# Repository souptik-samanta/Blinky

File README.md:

# Blinky Board

Made by Souptik!

I built this little project because I wanted a heart-shaped PCB that I could gift to someone. It's a simple LED chaser built around a 555 timer and a CD4017 decade counter. The LEDs light up one after another, creating a blinking animation around the heart.

Built using parts I already had on hand, and manufactured through JLC thanks stasis.
BUILD PHOTO

and here is the bottom

worknig video 

https://youtube.com/shorts/QsSJmAaTk8Q?feature=share
## Photos

## How It Works

A 555 timer is configured as an oscillator that generates clock pulses. These pulses are fed into a CD4017 decade counter, which turns on one output at a time. Each output drives an LED on the heart, creating a rotating blinking effect. The potentiometer can be adjusted to change the animation speed.

## Bill of Materials (BoM)

| Part | Purpose | Quantity |
|--------|---------|----------|
| PCB | Heart-shaped board that holds all the components | 1 |
| LED | Creates the chasing light effect around the heart | 10 |
| 1kΩ Resistor | Helps set the oscillator timing | 1 |
| 470Ω Resistor | Limits LED current | 1 |
| Potentiometer (RV) | Adjusts the animation speed | 1 |
| 1µF Capacitor | Works with the 555 timer to generate clock pulses | 1 |
| 1x01 Header | Test/debug connection point | 1 |
| 1x02 Header | Power input connector | 1 |
| CD4017 | Sequences the LEDs one after another | 1 |
| NE555P | Generates the clock signal | 1 |

## Cost

All components were sourced from my existing parts inventory, so the project itself cost me nothing to assemble.

| Item | Cost (USD) |
|--------|------------|
| Components | $0.00 |
| PCB | JLC sponser |
| **Total Out-of-Pocket Cost** | **$0.00** |

## Why I Made It

I wanted to make something small, simple, and fun that could be gifted to someone. Instead of a regular rectangular PCB, I designed it in the shape of a heart and added a classic 555 + 4017 LED chaser circuit to make it feel a bit more special.

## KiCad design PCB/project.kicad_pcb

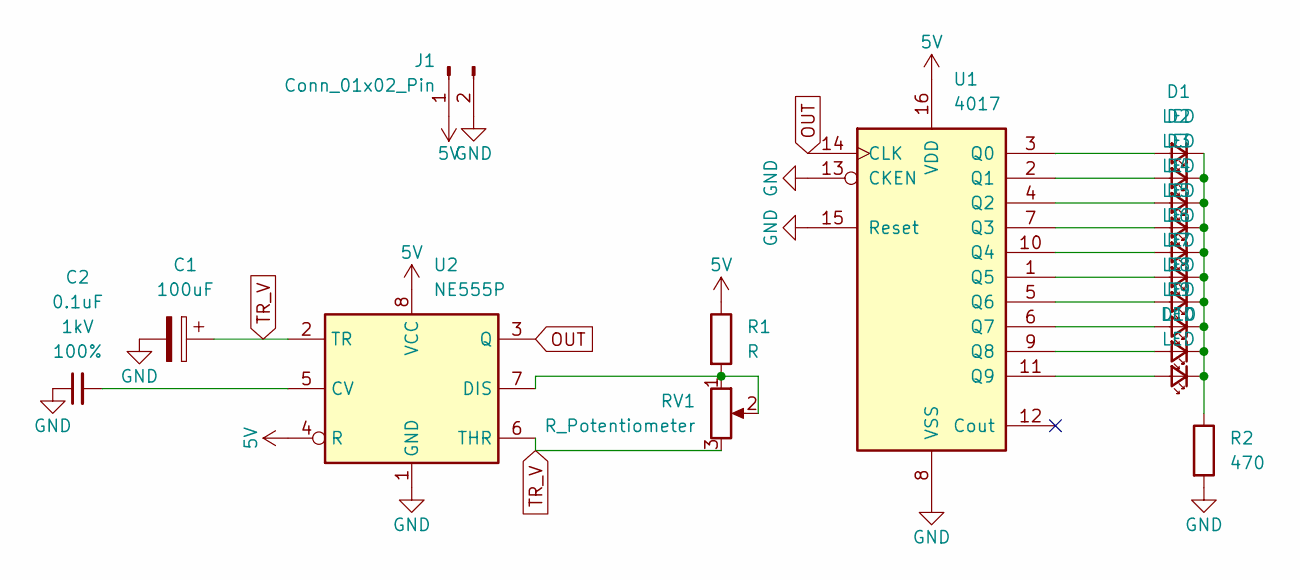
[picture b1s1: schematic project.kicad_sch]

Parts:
C1: 100uF; CP_Radial_D5.0mm_P2.50mm
C2: 0.1uF; C_Disc_D4.7mm_W2.5mm_P5.00mm; Voltage 1kV; Tolerance 100%
D1, D2, D3, D4, D5, D6, D7, D8, D9, D10: LED; LED_D5.0mm
J1: Conn_01x02_Pin; PinSocket_1x02_P2.54mm_Vertical
R1: R; R_Axial_DIN0207_L6.3mm_D2.5mm_P7.62mm_Horizontal
R2: 470; R_Axial_DIN0207_L6.3mm_D2.5mm_P7.62mm_Horizontal
RV1: R_Potentiometer; Potentiometer_Vishay_T93YA_Vertical
U1: 4017; DIP-16_W7.62mm_LongPads
U2: NE555P; DIP-8_W7.62mm_LongPads

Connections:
5V: J1.1, R1.1, U1.16 (VDD), U2.4 (R), U2.8 (VCC)
GND: C1.2, C2.1, J1.2, R2.2, U1.8 (VSS), U1.13 (CKEN), U1.15 (Reset), U2.1 (GND)
unnamed: D1.2 (A), U1.3 (Q0)
unnamed: D1.1 (K), D2.1 (K), D3.1 (K), D4.1 (K), D5.1 (K), D6.1 (K), D7.1 (K), D8.1 (K), D9.1 (K), D10.1 (K), R2.1
unnamed: D2.2 (A), U1.2 (Q1)
unnamed: D3.2 (A), U1.4 (Q2)
unnamed: D4.2 (A), U1.7 (Q3)
unnamed: D5.2 (A), U1.10 (Q4)
unnamed: D6.2 (A), U1.1 (Q5)
unnamed: D7.2 (A), U1.5 (Q6)
unnamed: D8.2 (A), U1.6 (Q7)
unnamed: D9.2 (A), U1.9 (Q8)
unnamed: D10.2 (A), U1.11 (Q9)
unnamed: C2.2, U2.5 (CV)
unnamed: R1.2, RV1.1, RV1.2, U2.7 (DIS)
OUT: U1.14 (CLK), U2.3 (Q)
TR_V: C1.1, RV1.3, U2.2 (TR), U2.6 (THR)

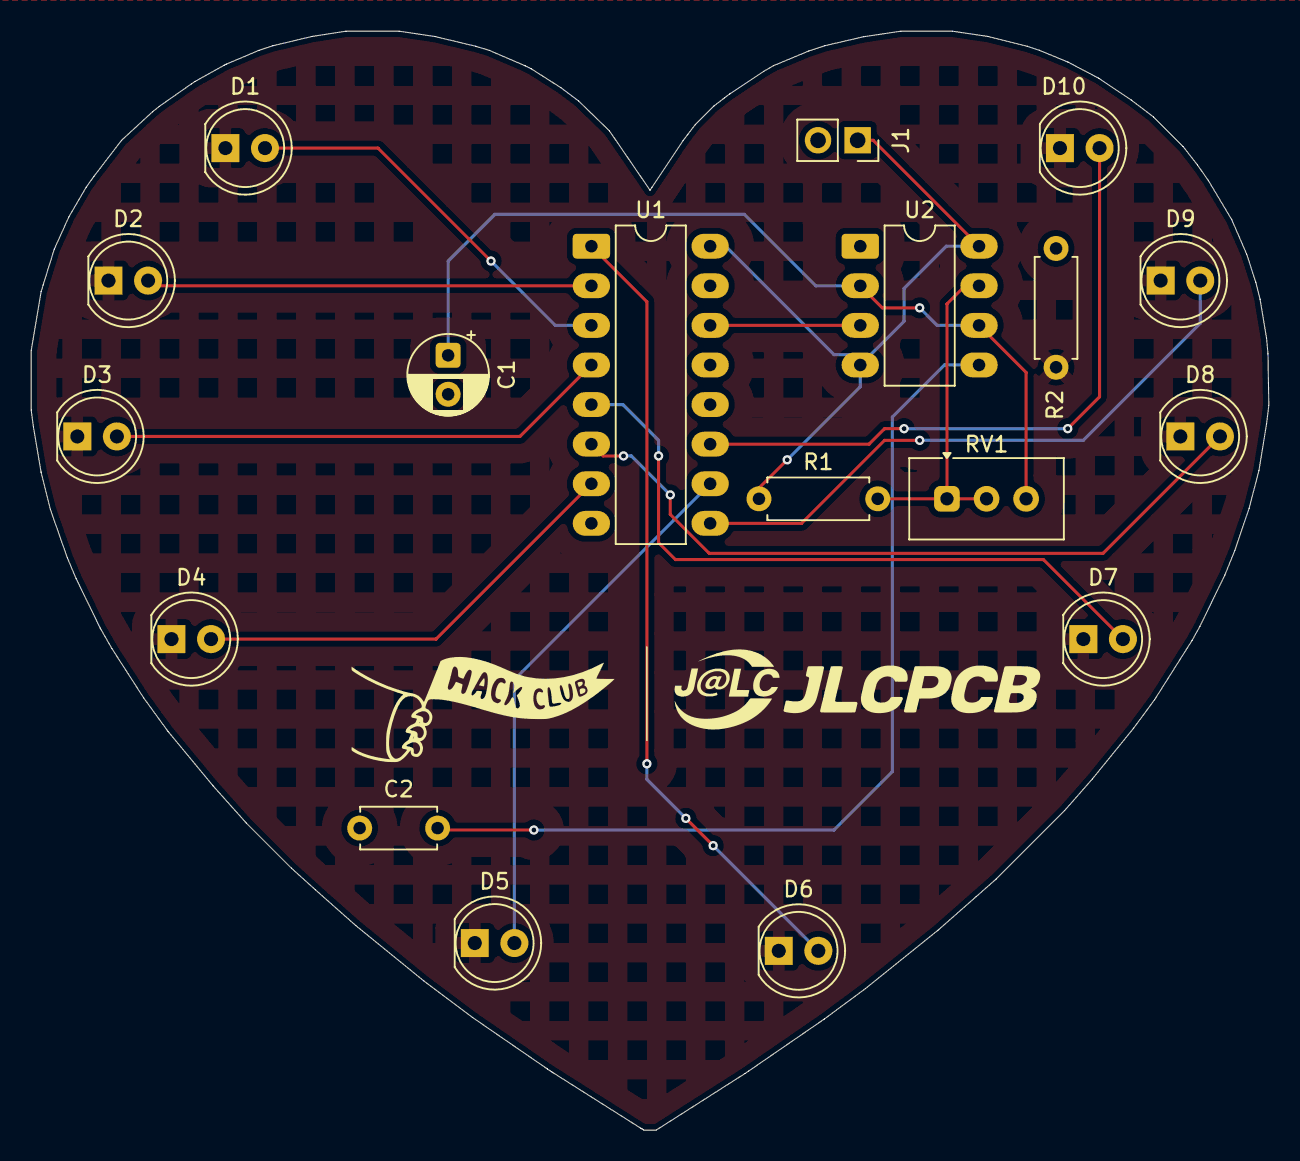
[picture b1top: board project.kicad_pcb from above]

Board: 2 copper layers, 79.4 x 70.5 mm, 18 parts (0 on the bottom side), 17 nets.

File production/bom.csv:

Designator,Footprint,Quantity,Value,LCSC Part #
C1,CP_Radial_D5.0mm_P2.50mm,1,100uF,
C2,C_Disc_D4.7mm_W2.5mm_P5.00mm,1,0.1uF,
"D1, D10, D2, D3, D4, D5, D6, D7, D8, D9",LED_D5.0mm,10,LED,
J1,PinSocket_1x02_P2.54mm_Vertical,1,Conn_01x02_Pin,
R1,R_Axial_DIN0207_L6.3mm_D2.5mm_P7.62mm_Horizontal,1,R,
R2,R_Axial_DIN0207_L6.3mm_D2.5mm_P7.62mm_Horizontal,1,470,
RV1,Potentiometer_Vishay_T93YA_Vertical,1,R_Potentiometer,
U1,DIP-16_W7.62mm_LongPads,1,4017,
U2,DIP-8_W7.62mm_LongPads,1,NE555P,

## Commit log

2026-06-13 DPME
2026-06-13 DOME
